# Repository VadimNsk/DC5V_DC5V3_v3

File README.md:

# DC5V_DC5V3_v3
Преобразователь DC/DC 5В в 5В и 3.3В с гальванической развязкой

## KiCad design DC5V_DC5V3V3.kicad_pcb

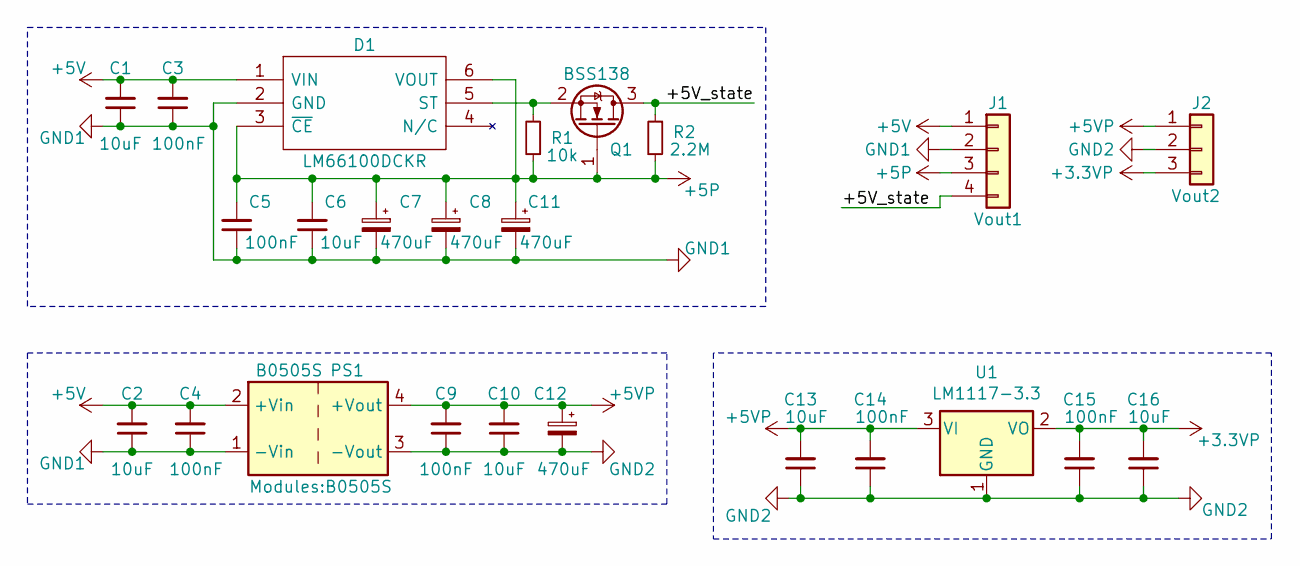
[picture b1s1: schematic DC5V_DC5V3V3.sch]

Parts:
C1, C2, C6, C10, C13, C16: 10uF; C_0603_1608Metric
C3, C4, C5, C9, C14, C15: 100nF; C_0603_1608Metric
C7, C8: 470uF; CP_EIA-7343-31_Kemet-D
C11, C12: 470uF; CP_EIA-7343-15_Kemet-W
D1: LM66100DCKR; SOP65P210X110-6N; Manufacturer_Part_Number LM66100DCKR; Mouser Part Number 595-LM66100DCKR
J1: Vout1; PinHeader_1x04_P2.54mm_Horizontal_short
J2: Vout2; PinHeader_1x03_P2.54mm_Horizontal_short
PS1: B0505S
Q1: BSS138; SOT-23
R1: 10k; R_0603_1608Metric
R2: 2.2M; R_0603_1608Metric
U1: LM1117-3.3; SOT-223-3_TabPin2

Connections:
+3.3VP: C15.2, C16.2, J2.3, U1.2 (VO)
+5P: C5.2, C6.2, C7.1, C8.1, C11.1, D1.3 (~CE), D1.6 (VOUT), J1.3, Q1.1 (G), R1.1, R2.2
+5V: C1.2, C2.2, C3.2, C4.2, D1.1 (VIN), J1.1, PS1.2 (+Vin)
+5VP: C9.2, C10.2, C12.1, C13.2, C14.2, J2.1, PS1.4 (+Vout), U1.3 (VI)
/+5V_state: J1.4, Q1.3 (D), R2.1
GND1: C1.1, C2.1, C3.1, C4.1, C5.1, C6.1, C7.2, C8.2, C11.2, D1.2 (GND), J1.2, PS1.1 (-Vin)
GND2: C9.1, C10.1, C12.2, C13.1, C14.1, C15.1, C16.1, J2.2, PS1.3 (-Vout), U1.1 (GND)
unnamed: D1.5 (ST), Q1.2 (S), R1.2

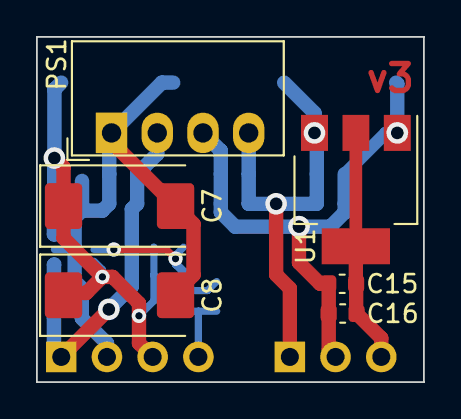
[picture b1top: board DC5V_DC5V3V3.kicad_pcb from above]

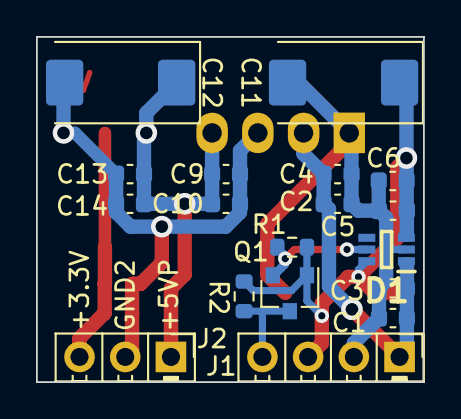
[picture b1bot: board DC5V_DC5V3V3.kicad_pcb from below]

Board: 2 copper layers, 21.5 x 19.2 mm, 24 parts (18 on the bottom side), 8 nets.

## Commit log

2021-11-27 Добавлены основные файлы в репозиторий.
2021-11-29 Разведена печатная плата в 2-х слоях
2021-12-25 Окончена трассировка печатной платы
2022-01-18 Первый вариант генерирования гербера.
2022-01-18 Добавлен BOM-файл в HTML-формате, гербера и файлы сверловки
2022-01-18 Сформирован перечень элементов, 3D-модель, исправлены ошибки, реализована панелизация платы.
2022-02-17 Последние изменения в BOM
